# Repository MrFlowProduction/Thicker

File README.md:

# Thicker
 NewLine vehicle ignition controller for OBU device

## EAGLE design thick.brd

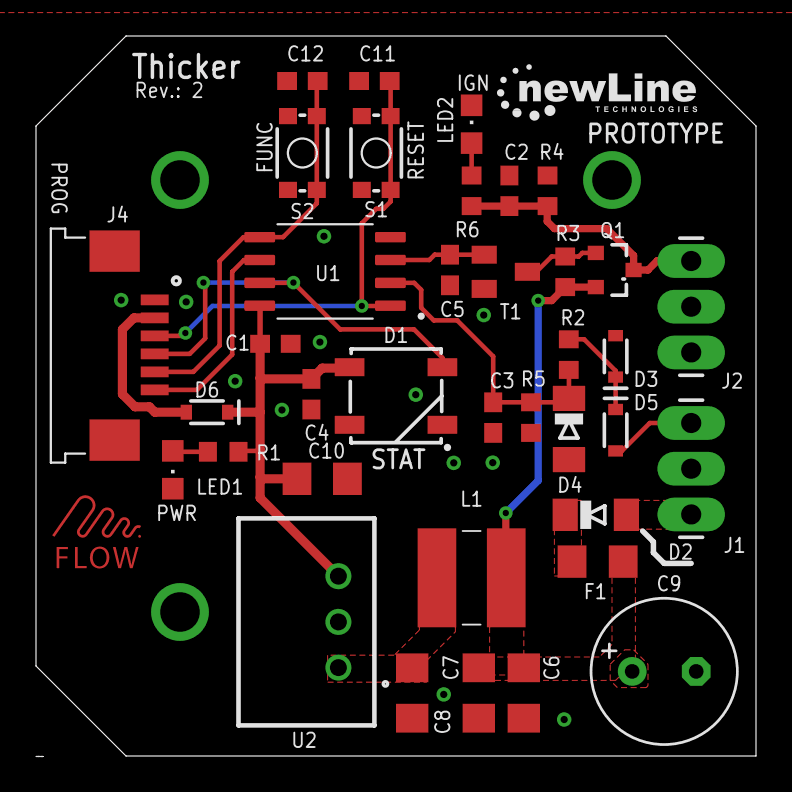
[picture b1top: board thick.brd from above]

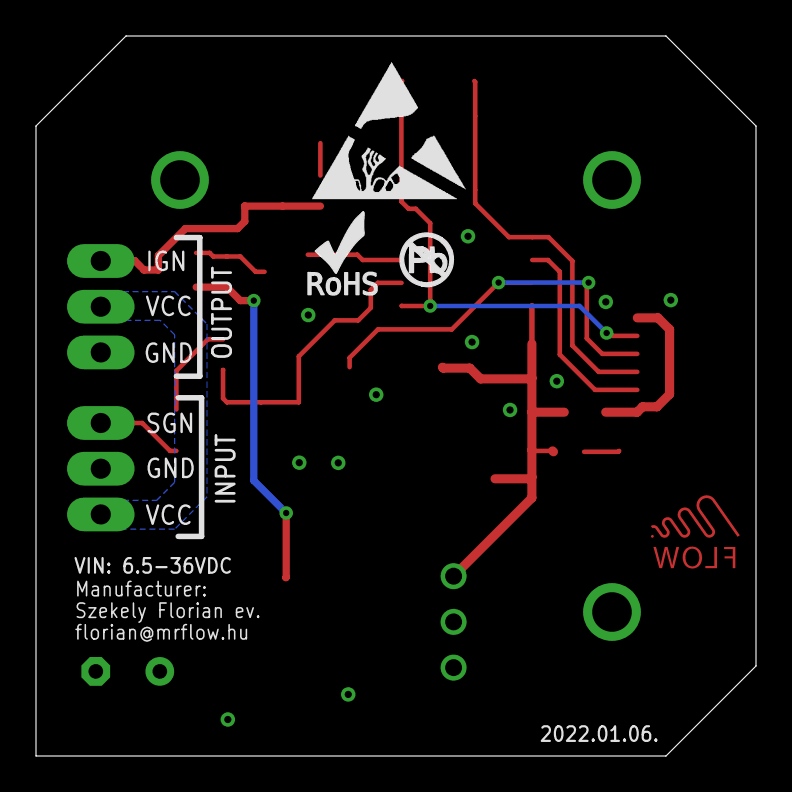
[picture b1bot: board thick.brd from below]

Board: 2 copper layers, 40.0 x 40.0 mm, 41 parts (3 on the bottom side), 19 nets.

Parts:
C1, C2, C5, C11, C12: 0.1uF; C0603
C3, C4: 1uF; C0603
C6, C7, C8, C10: 4.7uF; C1206
C9: 100uF; E3,5-8
D1: WS2812B
D2: MINIMELF
D3: tvs; SOD-323
D4: 5.6V; MINIMELF
D5, D6: 0.5A/40V/420mV; SOD-323
F1: R1206
J1, J2: 1X03_LONGPADS
J4: F1003WR-S-06PT; 1X06-1MM
L1: TCK-047; TCK047
LED1, LED2: CHIPLED_0805
Q1: SI2319DDS-T1-GE3; SOT23-3
R1, R3, R4, R6: 10K; R0603
R2: 120K; R0603
R5: 22K; R0603
S1, S2: TACTILE_SWITCH_SMD_4.6X2.8MM
T1: SC59-BEC
U1: ATTINY85-20SU; SOIC127P798X216-8N
U2: TSR_0.5-2450; TSR-0.5-2433
U$1: ESD_LOGO
U$2: NO_PB_LOGO_0.120
U$3: ROHS_LOGO_0.18_IN
U$5: MRFLOW_7_5MM

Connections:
5V: C1.1, C4.1, C10.1, D1.1, D6.C, R1.1, U1.8, U2.3
!RESET: C11.1, J4.3, S1.1, S1.2, U1.1
AIN: C3.1, D4.C, R2.2, R5.2, U1.2
GND: C1.2, C2.2, C3.2, C4.2, C5.2, C6.2, C7.2, C8.2, C9.-, C10.2, C11.2, C12.2, D1.3, D3.A, D4.A, J1.2, J2.3, J4.1, LED1.C, LED2.C, R4.1, R5.1, S1.3, S1.4, S2.3, S2.4, T1.E, U1.4, U2.2
IGNITION: C2.1, J2.1, Q1.3, R4.2, R6.1
IGN_EN: C5.1, T1.B, U1.3
MISO: J4.6, U1.6
MOSI: C12.1, J4.5, S2.1, S2.2, U1.5
unnamed: Q1.1, R3.1, T1.C
unnamed: C8.1, L1.2, U2.1
unnamed: LED1.A, R1.2
unnamed: LED2.A, R6.2
unnamed: D6.A, J4.2
unnamed: D3.C, D5.C, R2.1
unnamed: D2.C, F1.1
SCK: D1.4, J4.4, U1.7
SIGNAL: D5.A, J1.1
VCC: D2.A, J1.3, J2.2
VDD: C6.1, C7.1, C9.+, F1.2, L1.1, Q1.2, R3.2

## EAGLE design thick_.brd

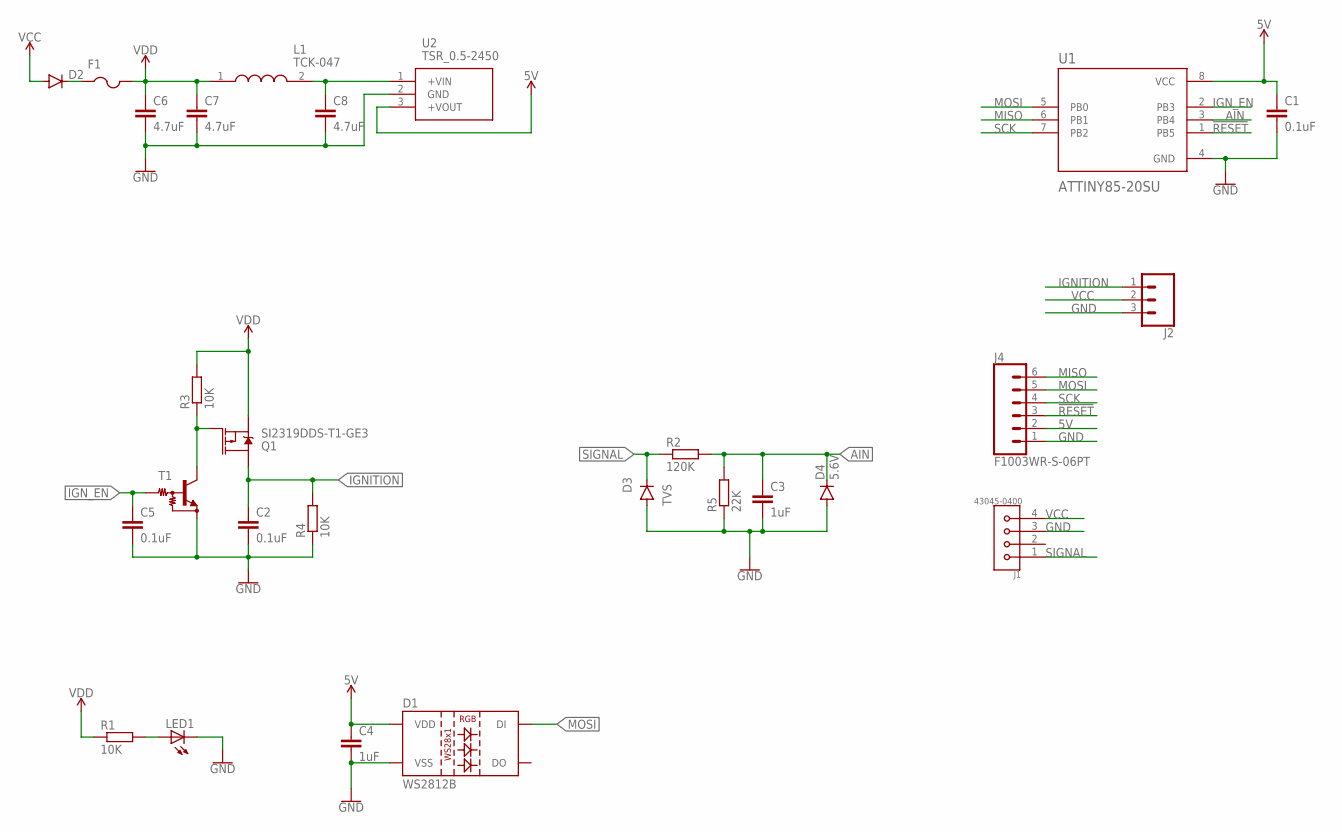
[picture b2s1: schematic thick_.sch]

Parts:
C1, C2, C5: 0.1uF; C0603
C3, C4: 1uF; C0603
C6, C7, C8: 4.7uF; C1206
D1: WS2812B
D2: DIODE-MINIMELF; MINIMELF
D3: TVS; DO214AC
D4: 5.6V; MINIMELF
F1: PTCFUSE-1206; R1206
J1: 43045-0400; MOLEX_43045-0400
J2: CONN_03LONGPADS; 1X03_LONGPADS
J4: F1003WR-S-06PT; 1X06-1MM
L1: TCK-047; TCK047
LED1: LEDCHIPLED_0805; CHIPLED_0805
Q1: SI2319DDS-T1-GE3; SOT23-3
R1, R3, R4: 10K; R0603
R2: 120K; R0603
R5: 22K; R0603
T1: MUN2213T1-NPN_DRIVER-SC59-BEC; SC59-BEC
U1: ATTINY85-20SU; SOIC127P798X216-8N
U2: TSR_0.5-2450; TSR-0.5-2433

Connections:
5V: C1.1, C4.1, D1.1 (VDD), J4.2, U1.8 (VCC), U2.3 (+VOUT)
!RESET: J4.3, U1.1 (PB5)
AIN: C3.1, D4.C, R2.2, R5.2, U1.3 (PB4)
GND: C1.2, C2.2, C3.2, C4.2, C5.2, C6.2, C7.2, C8.2, D1.3 (VSS), D3.A, D4.A, J1.3, J2.3, J4.1, LED1.C, R4.1, R5.1, T1.E, U1.4 (GND), U2.2 (GND)
IGNITION: C2.1, J2.1, Q1.3 (D), R4.2
IGN_EN: C5.1, T1.B, U1.2 (PB3)
MISO: J4.6, U1.6 (PB1)
MOSI: D1.4 (DI), J4.5, U1.5 (PB0)
unnamed: Q1.1 (G), R3.1, T1.C
unnamed: C8.1, L1.2, U2.1 (+VIN)
unnamed: LED1.A, R1.2
unnamed: D2.C, F1.1
SCK: J4.4, U1.7 (PB2)
SIGNAL: D3.C, J1.1, R2.1
VCC: D2.A, J1.4, J2.2
VDD: C6.1, C7.1, F1.2, L1.1, Q1.2 (S), R1.1, R3.2

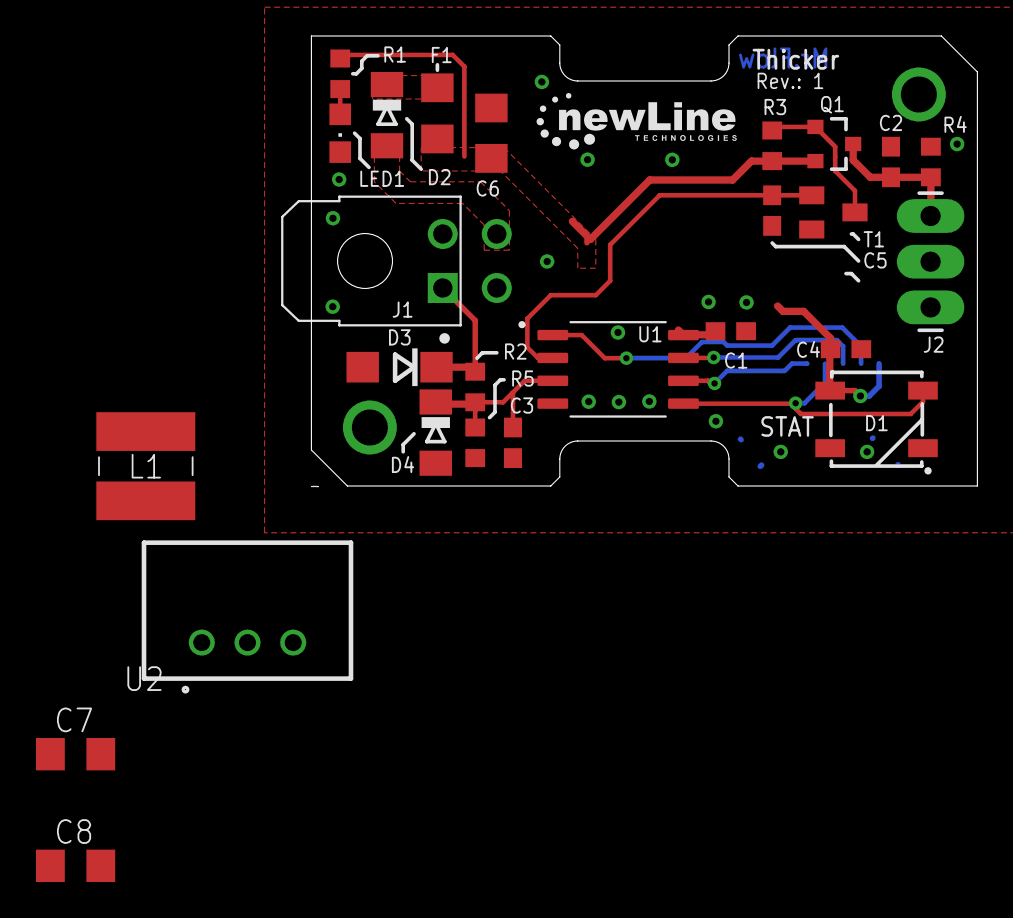
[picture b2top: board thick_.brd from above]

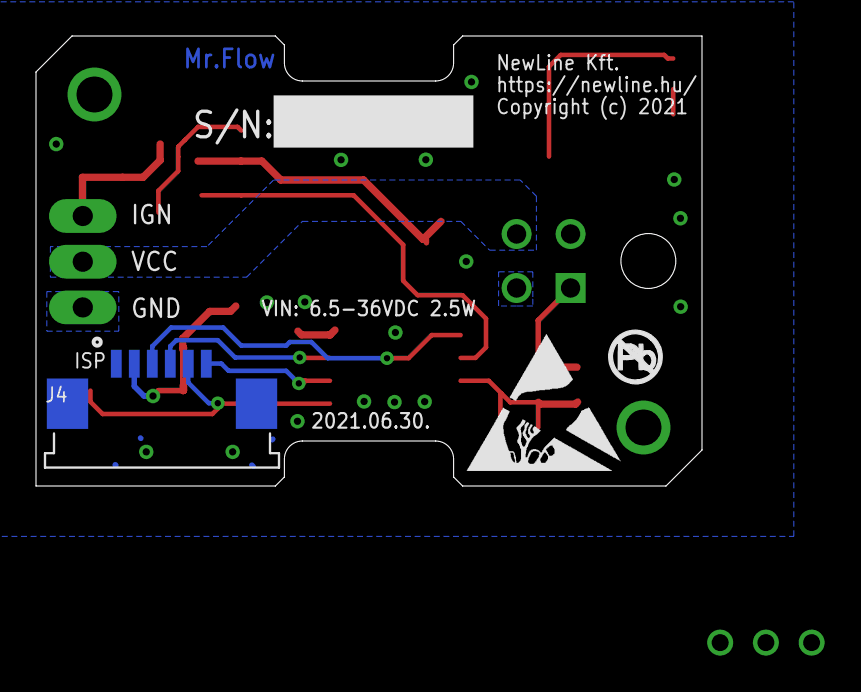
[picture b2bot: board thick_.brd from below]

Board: 2 copper layers, 37.0 x 25.0 mm, 29 parts (3 on the bottom side), 16 nets.

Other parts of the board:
U$1: ESD_LOGO
U$2: NO_PB_LOGO_0.120

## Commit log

2021-05-20 Rev 1 + Gerbers
    Revolution 1 and Gerbers for prototype
2021-06-23 Gerbers
2021-06-30 Fixing
    - sizes
    - FPC connector
    - Molex connector
2021-07-18 Javított végleges
2022-01-25 rev 2
    new pcb design with gerbers

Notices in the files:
thick_.brd:
Copyright (c) 2021
parts and their libraries:
SparkFun-DiscreteSemi: Licensing: Creative Commons ShareAlike 4.0 International - https://creativecommons.org/licenses/by-sa/4.0
